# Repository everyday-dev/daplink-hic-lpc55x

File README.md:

# We've moved. 
In an effort to truly own and be in full control of our clients and personal information, source code, and documentation we've moved to a self-hosted Git server. You can find this project here: [git.everydaydev.io](https://git.everydaydev.io/opensource/daplink-hic-lpc55x)

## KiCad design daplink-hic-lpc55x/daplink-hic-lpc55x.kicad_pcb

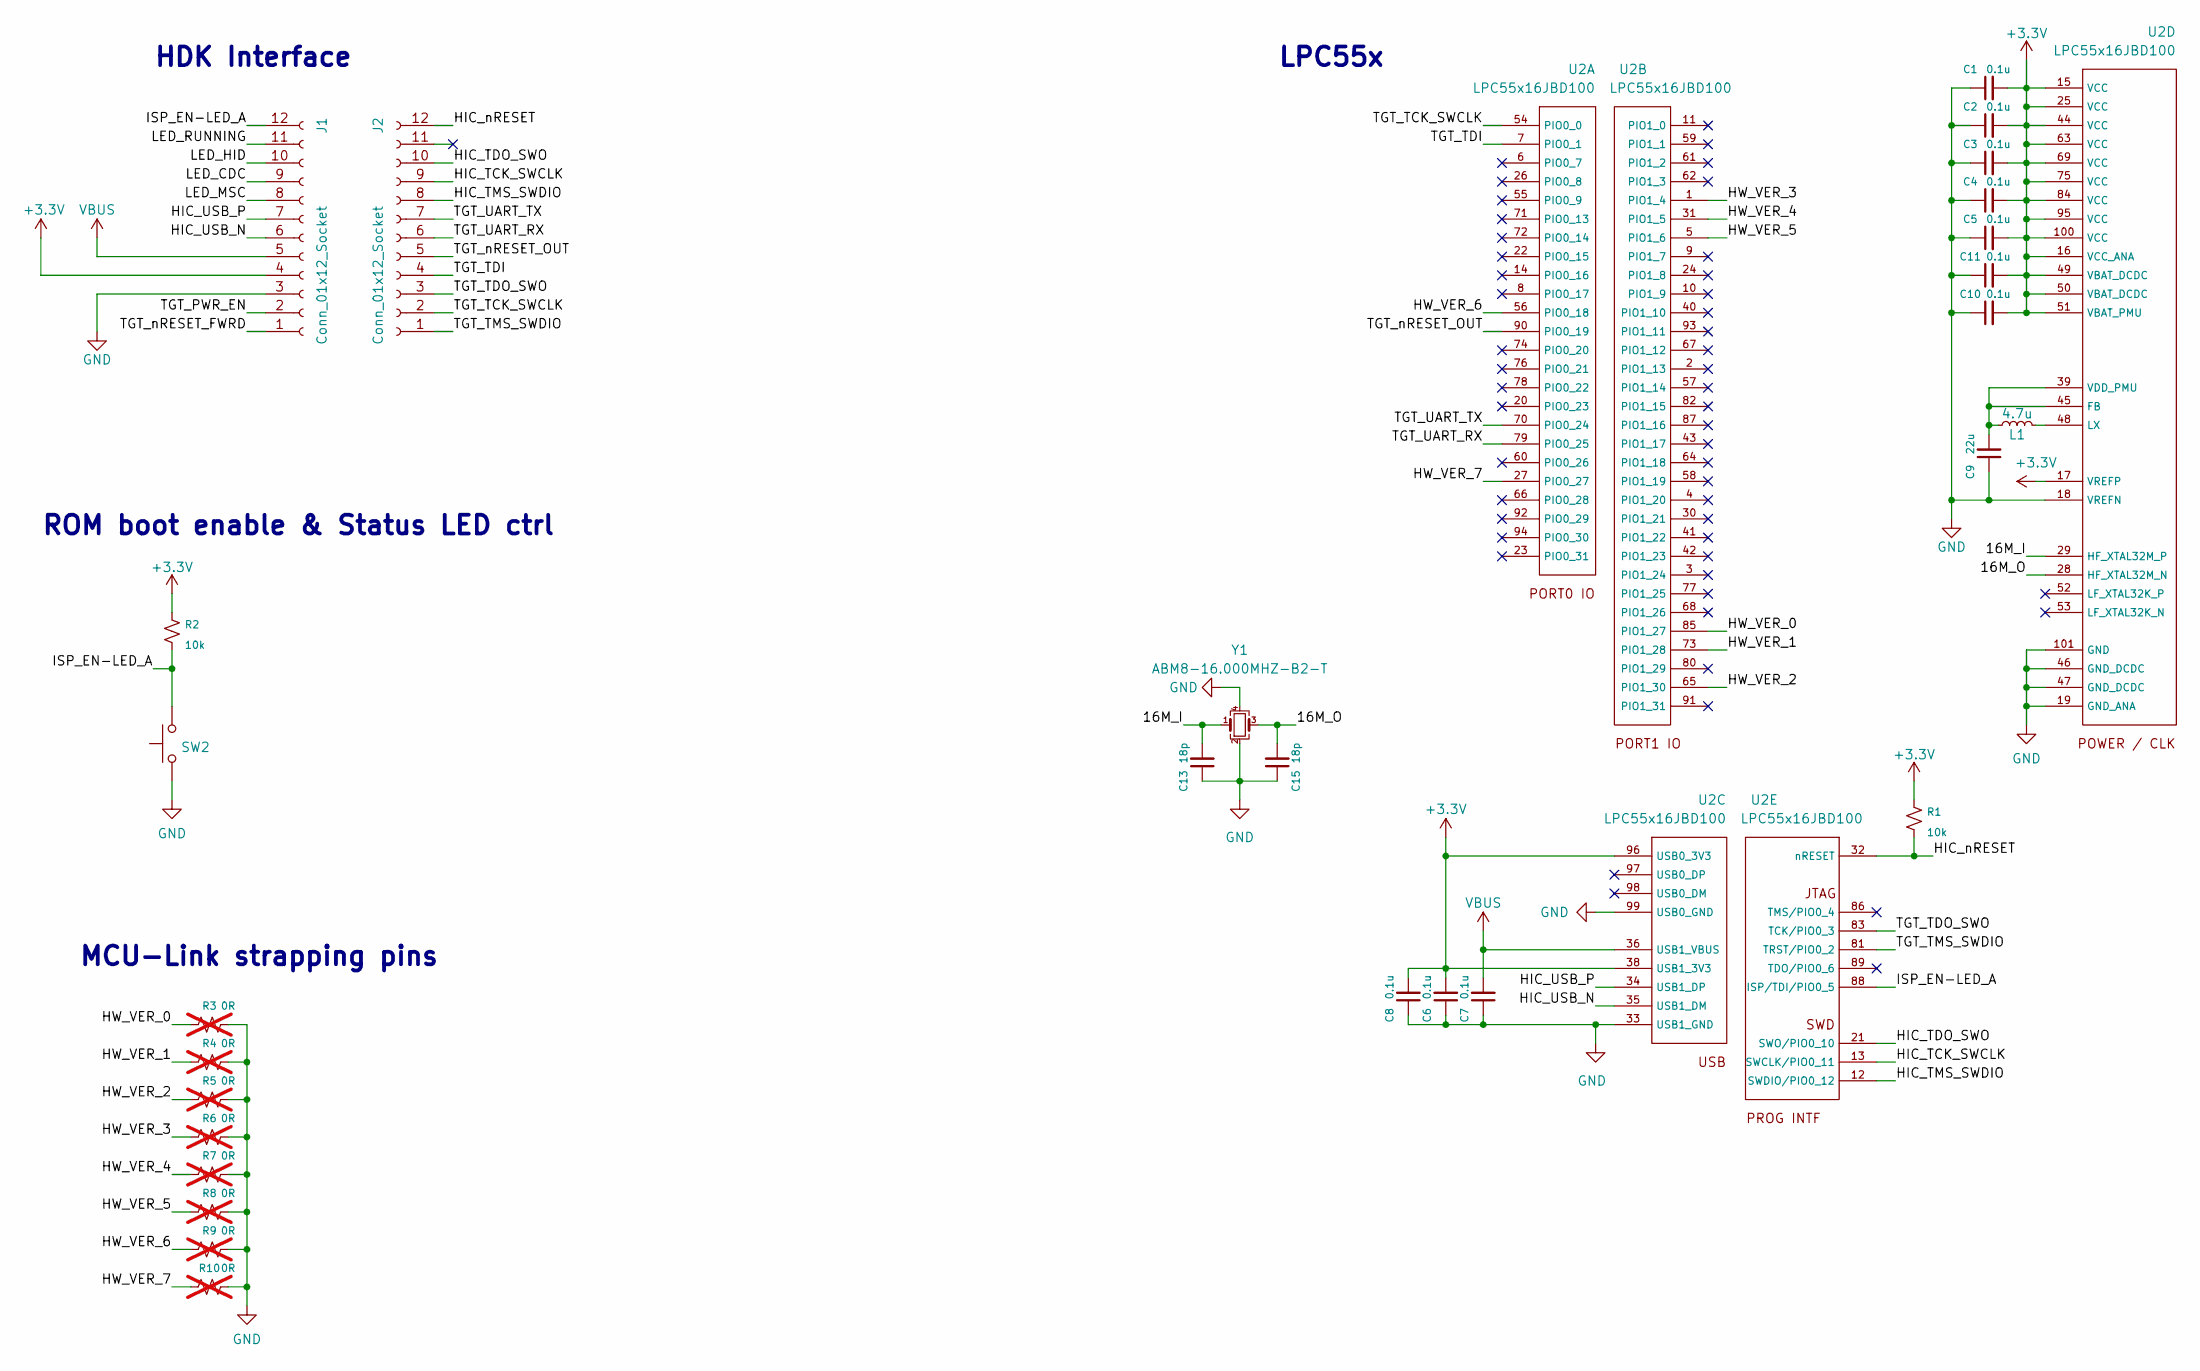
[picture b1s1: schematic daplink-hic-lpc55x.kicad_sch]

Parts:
C1, C2, C3, C4, C5, C6, C7, C8, C10, C11: 0.1u; C_0402_1005Metric; MPN CC0402KRX7R7BB104
C9: 22u; C_0603_1608Metric; MPN CC0603MRX5R5BB226
C13, C15: 18p; C_0402_1005Metric; MPN CC0402JRNPO9BN180
J1, J2: Conn_01x12_Socket; PinHeader_1x12_P2.54mm_Vertical; MPN PH1-12-UA
L1: 4.7u; L_0805_2012Metric; MPN MLZ2012N4R7LT000
R1, R2: 10k; R_0402_1005Metric; MPN RC0402JR-0710KL
R3, R4, R5, R6, R7, R8, R9, R10: 0R; R_0603_1608Metric; MPN RC0603FR-070RL; not fitted
SW2: SW_Push; Panasonic_EVQPUJ_EVQPUA; MPN EVQ-P7A01P
U2: LPC55x16JBD100; QFP-100_14x14_Pitch0.5mm; MPN LPC5516JBD100E
Y1: ABM8-16.000MHZ-B2-T; Crystal_SMD_3225-4Pin_3.2x2.5mm; MPN ABM8-16.000MHZ-B2-T

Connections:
+3V3: C1.2, C2.2, C3.2, C4.2, C5.2, C6.2, C8.2, C10.2, C11.2, J1.4, R1.1, R2.1, U2.15 (VCC), U2.16 (VCC_ANA), U2.17 (VREFP), U2.25 (VCC), U2.38 (USB1_3V3), U2.44 (VCC), U2.49 (VBAT_DCDC), U2.50 (VBAT_DCDC), U2.51 (VBAT_PMU), U2.63 (VCC), U2.69 (VCC), U2.75 (VCC), U2.84 (VCC), U2.95 (VCC), U2.96 (USB0_3V3), U2.100 (VCC)
/16M_I: C13.2, U2.29 (HF_XTAL32M_P), Y1.1
/16M_O: C15.2, U2.28 (HF_XTAL32M_N), Y1.3
/HIC_TCK_SWCLK: J2.9, U2.13 (SWCLK/PIO0_11)
/HIC_TDO_SWO: J2.10, U2.21 (SWO/PIO0_10)
/HIC_TMS_SWDIO: J2.8, U2.12 (SWDIO/PIO0_12)
/HIC_USB_N: J1.6, U2.35 (USB1_DM)
/HIC_USB_P: J1.7, U2.34 (USB1_DP)
/HIC_nRESET: J2.12, R1.2, U2.32 (nRESET)
/HW_VER_0: R3.2, U2.85 (PIO1_27)
/HW_VER_1: R4.2, U2.73 (PIO1_28)
/HW_VER_2: R5.2, U2.65 (PIO1_30)
/HW_VER_3: R6.2, U2.1 (PIO1_4)
/HW_VER_4: R7.2, U2.31 (PIO1_5)
/HW_VER_5: R8.2, U2.5 (PIO1_6)
/HW_VER_6: R9.2, U2.56 (PIO0_18)
/HW_VER_7: R10.2, U2.27 (PIO0_27)
/ISP_EN-LED_A: J1.12, R2.2, SW2.2, U2.88 (ISP/TDI/PIO0_5)
/LED_CDC: J1.9
/LED_HID: J1.10
/LED_MSC: J1.8
/LED_RUNNING: J1.11
/TGT_PWR_EN: J1.2
/TGT_TCK_SWCLK: J2.2, U2.54 (PIO0_0)
/TGT_TDI: J2.4, U2.7 (PIO0_1)
/TGT_TDO_SWO: J2.3, U2.83 (TCK/PIO0_3)
/TGT_TMS_SWDIO: J2.1, U2.81 (TRST/PIO0_2)
/TGT_UART_RX: J2.6, U2.79 (PIO0_25)
/TGT_UART_TX: J2.7, U2.70 (PIO0_24)
/TGT_nRESET_FWRD: J1.1
/TGT_nRESET_OUT: J2.5, U2.90 (PIO0_19)
GND: C1.1, C2.1, C3.1, C4.1, C5.1, C6.1, C7.1, C8.1, C9.1, C10.1, C11.1, C13.1, C15.1, J1.3, R3.1, R4.1, R5.1, R6.1, R7.1, R8.1, R9.1, R10.1, SW2.1, U2.18 (VREFN), U2.19 (GND_ANA), U2.33 (USB1_GND), U2.37 (USB1_GND), U2.46 (GND_DCDC), U2.47 (GND_DCDC), U2.99 (USB0_GND), U2.101 (GND), Y1.2, Y1.4
unnamed: C9.2, L1.1, U2.39 (VDD_PMU), U2.45 (FB)
unnamed: L1.2, U2.48 (LX)
VBUS: C7.2, J1.5, U2.36 (USB1_VBUS)

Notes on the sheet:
ROM boot enable & Status LED ctrl
MCU-Link strapping pins
LPC55x
HDK Interface

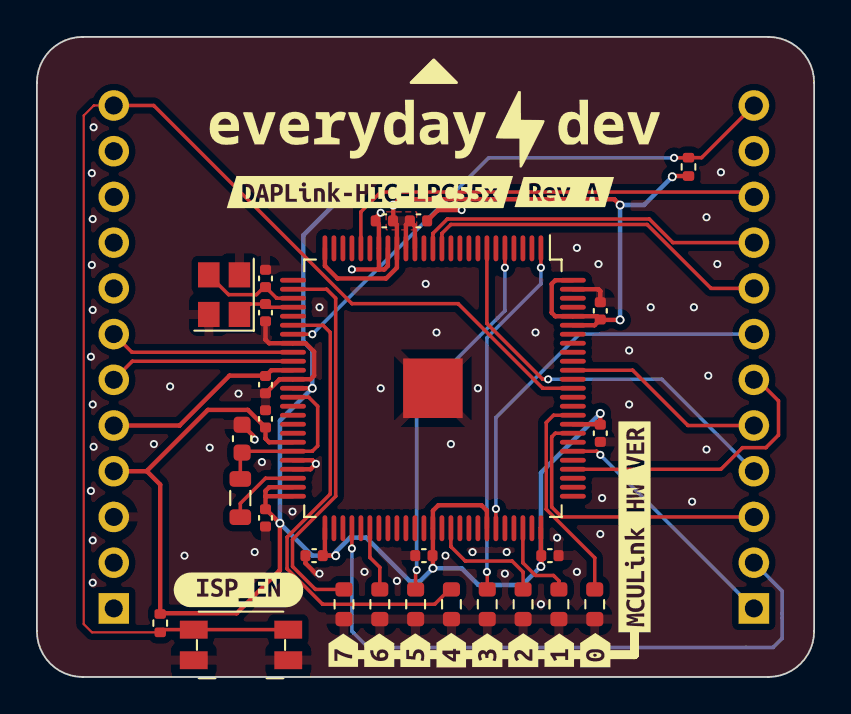
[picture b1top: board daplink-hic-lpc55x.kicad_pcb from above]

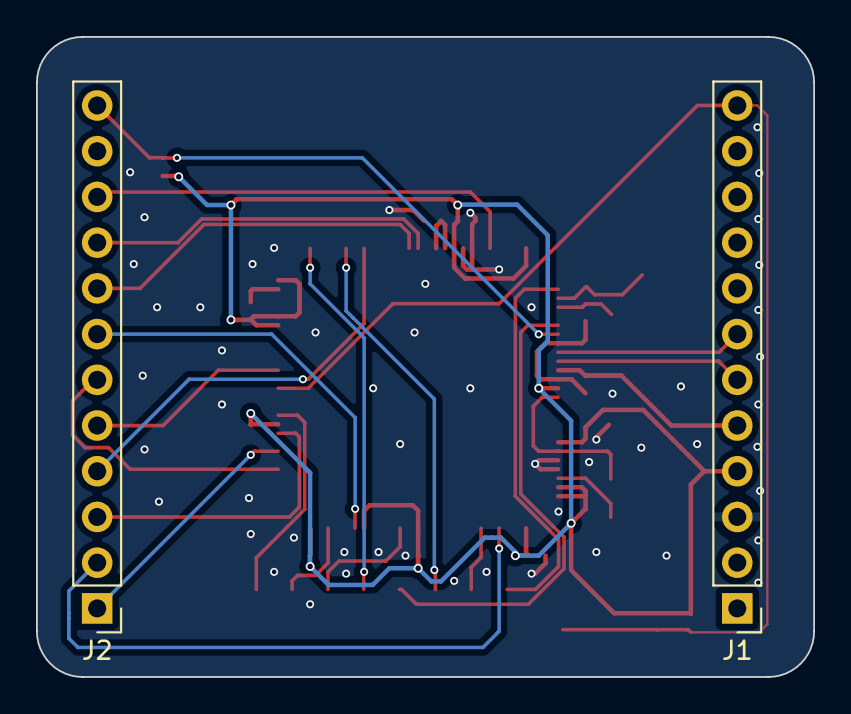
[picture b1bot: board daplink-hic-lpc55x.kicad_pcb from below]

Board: 2 copper layers, 43.2 x 35.6 mm, 41 parts (2 on the bottom side), 29 nets.

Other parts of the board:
kibuzzard-6548E80B: G***; kibuzzard-6548E80B
kibuzzard-6548ED42: G***; kibuzzard-6548ED42
kibuzzard-6554FF4C: G***; kibuzzard-6554FF4C
kibuzzard-656792B8: G***; kibuzzard-656792B8
kibuzzard-6567926A: G***; kibuzzard-6567926A
kibuzzard-6567926F: G***; kibuzzard-6567926F
kibuzzard-6567927C: G***; kibuzzard-6567927C
kibuzzard-65679241: G***; kibuzzard-65679241
kibuzzard-65679263: G***; kibuzzard-65679263
kibuzzard-65679267: G***; kibuzzard-65679267
kibuzzard-65679272: G***; kibuzzard-65679272
kibuzzard-65679278: G***; kibuzzard-65679278

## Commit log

2023-12-01 Reviwed and ready for release
2023-12-01 Added github CI files
2023-12-01 Added python utils needed for CI
2023-12-05 Update LPC package to the 100LQFP
2023-12-05 Update README img
2023-12-05 Add MPN info for the LPC55x
2023-12-05 Set min drill size to .25mm to get out of advanced process

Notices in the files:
daplink-hic-lpc55x/daplink-hic-lpc55x.kicad_sch:
License: CC-BY-SA
